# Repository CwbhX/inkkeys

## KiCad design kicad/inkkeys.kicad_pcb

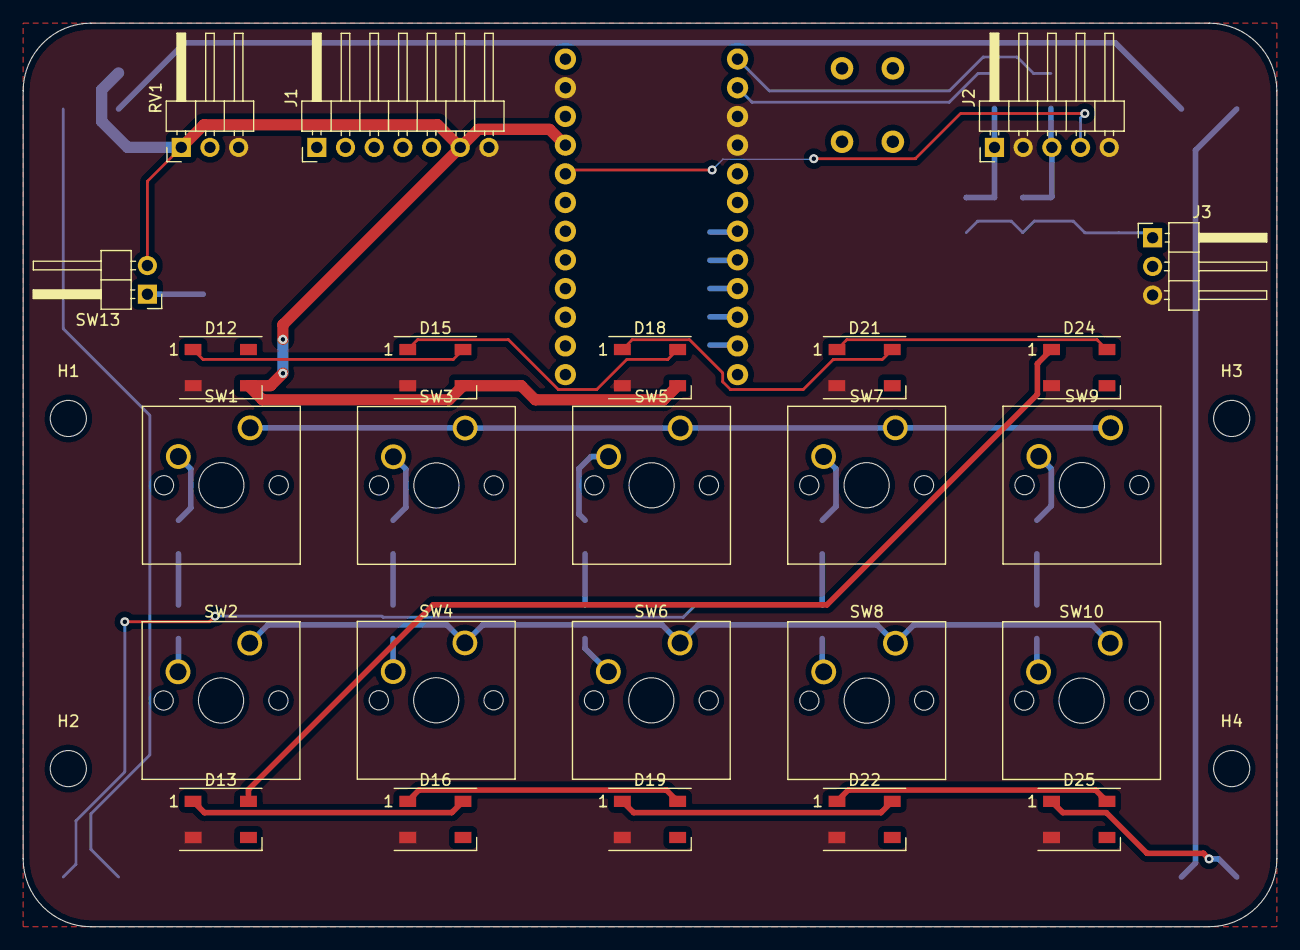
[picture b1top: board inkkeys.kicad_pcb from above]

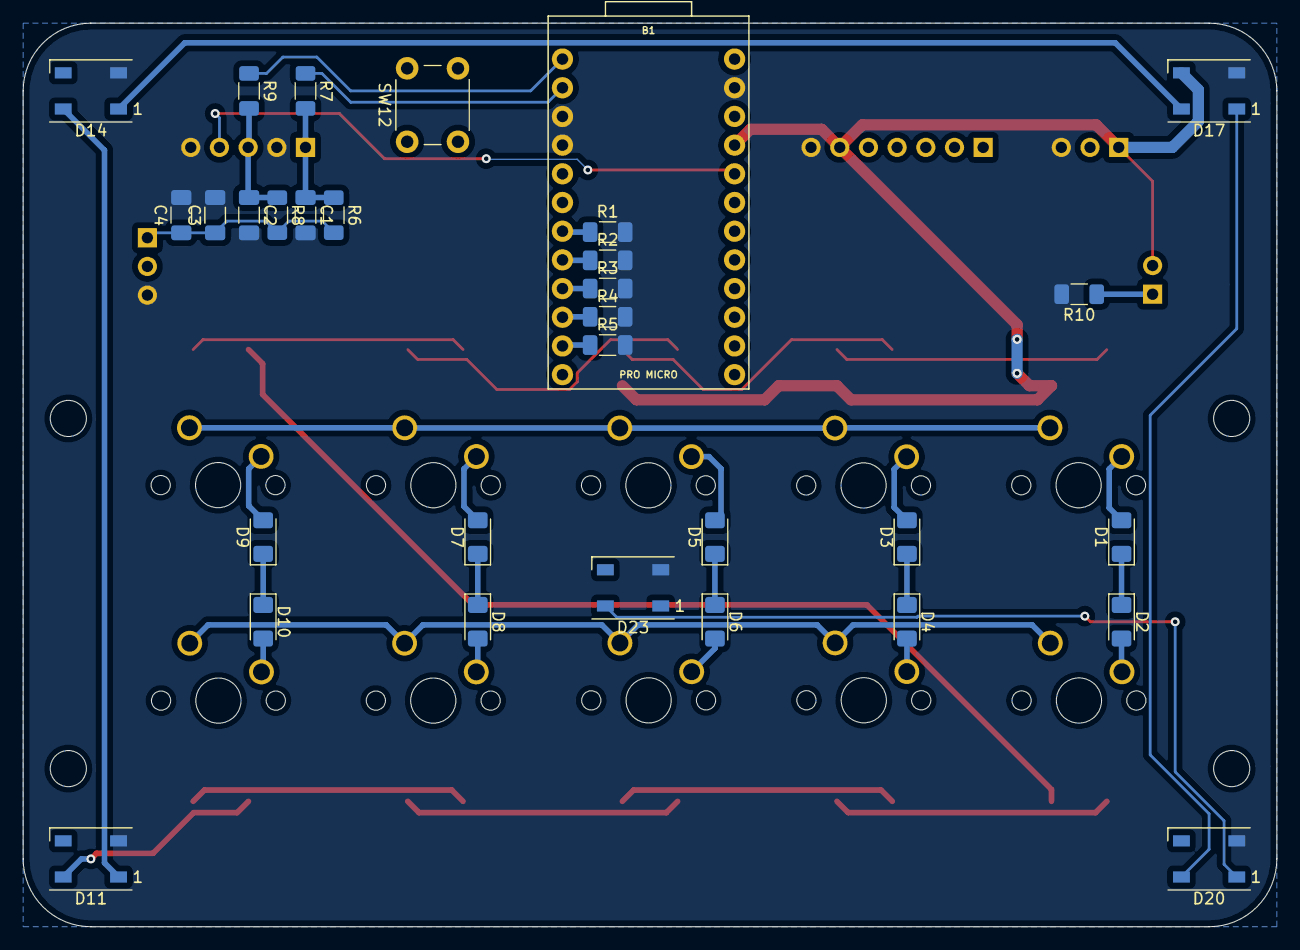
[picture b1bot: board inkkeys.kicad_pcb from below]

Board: 2 copper layers, 111.0 x 80.0 mm, 60 parts (31 on the bottom side), 48 nets.

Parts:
B1: PRO MICRO; SPARKFUN_PRO_MICRO
C1, C2: 10n; C_1206_3216Metric_Pad1.33x1.80mm_HandSolder
C3: 10nF; C_1206_3216Metric_Pad1.33x1.80mm_HandSolder
C4: 10uF; C_1206_3216Metric_Pad1.33x1.80mm_HandSolder
D1, D2, D3, D4, D5, D6, D7, D8, D9, D10: D; D_1206_3216Metric_Pad1.42x1.75mm_HandSolder
D11, D12, D13, D14, D15, D16, D17, D18, D19, D20, D21, D22, D23, D24, D25: WS2812B; LED_WS2812B_PLCC4_5.0x5.0mm_P3.2mm
H1, H2, H3, H4: MountingHole; MountingHole_3.2mm_M3
J1: Conn_01x07; PinHeader_1x07_P2.54mm_Horizontal
J2: Conn_01x05; PinHeader_1x05_P2.54mm_Horizontal
J3: Conn_01x03; PinHeader_1x03_P2.54mm_Horizontal
R1, R2, R3, R4, R5, R6, R7, R8, R9, R10: 10k; R_1206_3216Metric_Pad1.30x1.75mm_HandSolder
RV1: R_POT; PinHeader_1x03_P2.54mm_Horizontal
SW1, SW2, SW3, SW4, SW5, SW6, SW7, SW8, SW9, SW10: SW_Push; SW_Cherry_MX_1.00u_PCB
SW12: SW_MEC_5G; SW_PUSH_6mm_H5mm
SW13: SW_DPST_x2; PinHeader_1x02_P2.54mm_Horizontal

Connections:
+5V: B1.21, C3.1, C4.1, D11.3, D12.3, D13.3, D14.3, D15.3, D16.3, D17.3, D18.3, D19.3, D20.3, D21.3, D22.3, D23.3, D24.3, D25.3, J1.6, J3.1, R6.2, R8.2, RV1.1, SW13.2
/Col1: B1.7, D1.1, D2.1, R1.1
/Col2: B1.8, D3.1, D4.1, R2.1
/Col3: B1.9, D5.1, D6.1, R3.1
/Col4: B1.10, D7.1, D8.1, R4.1
/Col5: B1.11, D9.1, D10.1, R5.1
/OLED_CS: B1.18, J1.1
/OLED_DC: B1.17, J1.2
/OLED_RES: B1.15, J1.3
/OLED_SCL: B1.16, J1.5
/OLED_SDA: B1.14, J1.4
/RA: C1.1, J2.1, R6.1, R7.2
/RC: C2.1, J2.3, R8.1, R9.2
/RGB_D_OUT: B1.19, D12.4
/RS1: B1.20, J2.4
/Row1: B1.5, SW1.1, SW3.1, SW5.1, SW7.1, SW9.1
/Row2: B1.6, SW2.1, SW4.1, SW6.1, SW8.1, SW10.1
/SLIDER_OUT: B1.12, RV1.2
GND: B1.3, B1.4, B1.23, C1.2, C2.2, C3.2, C4.2, D11.2, D12.2, D13.2, D14.2, D15.2, D16.2, D17.2, D18.2, D19.2, D20.2, D21.2, D22.2, D23.2, D24.2, D25.2, J1.7, J2.2, J2.5, J3.3, R1.2, R2.2, R3.2, R4.2, R5.2, R10.2, RV1.3
unnamed: B1.1, R9.1
unnamed: B1.2, R7.1
unnamed: B1.13, R10.1, SW13.1
unnamed: B1.22, SW12.1, SW12.2
unnamed: D1.2, SW1.2
unnamed: D2.2, SW2.2
unnamed: D3.2, SW3.2
unnamed: D4.2, SW4.2
unnamed: D5.2, SW5.2
unnamed: D6.2, SW6.2
unnamed: D7.2, SW7.2
unnamed: D8.2, SW8.2
unnamed: D9.2, SW9.2
unnamed: D10.2, SW10.2
unnamed: D11.1, D14.4
unnamed: D11.4, D25.1
unnamed: D12.1, D15.4
unnamed: D13.1, D16.4
unnamed: D13.4, D24.1
unnamed: D14.1, D17.4
unnamed: D15.1, D18.4
unnamed: D16.1, D19.4
unnamed: D17.1, D20.4
unnamed: D18.1, D21.4
unnamed: D19.1, D22.4
unnamed: D20.1, D23.4
unnamed: D21.1, D24.4
unnamed: D22.1, D25.4
unnamed: D23.1, J3.2

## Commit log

2021-05-09 Completed most of new schematic
    CHANGES:
    - Added reference images
    - Removed old LEDs
    - Added Keyswitch matrix
    - Added OLED connector
    - Added Slider
2021-05-13 1. Added Requirements.txt and 2. Removed linux volume library
2021-05-13 Added Gitignore
2021-05-13 Updated labels and added footprints
2021-05-13 PCB Layout started
2021-05-17 Working changes from Nakul
2021-05-17 Getting there
2021-05-17 Updated Cad Files
    Created a new bottom of case that is thicker and fits PCB better
2021-05-17 Bunch of changes, got the preform integration working
2021-05-17 Modes for preform knob editor
2021-05-17 PCB Work
2021-05-18 Logo and Credits
2021-05-28 Lowered the LED brightness for test
2021-05-30 preliminary setup for matrixes
2021-06-04 Finished PCB and Generated Gerbers
2021-06-19 Cleaned up comments on the new modes we made
2021-06-19 added back old modes
2021-06-19 Updated gitignore
2021-06-19 removed files that shouldn't be tracked
2021-07-06 added step file
